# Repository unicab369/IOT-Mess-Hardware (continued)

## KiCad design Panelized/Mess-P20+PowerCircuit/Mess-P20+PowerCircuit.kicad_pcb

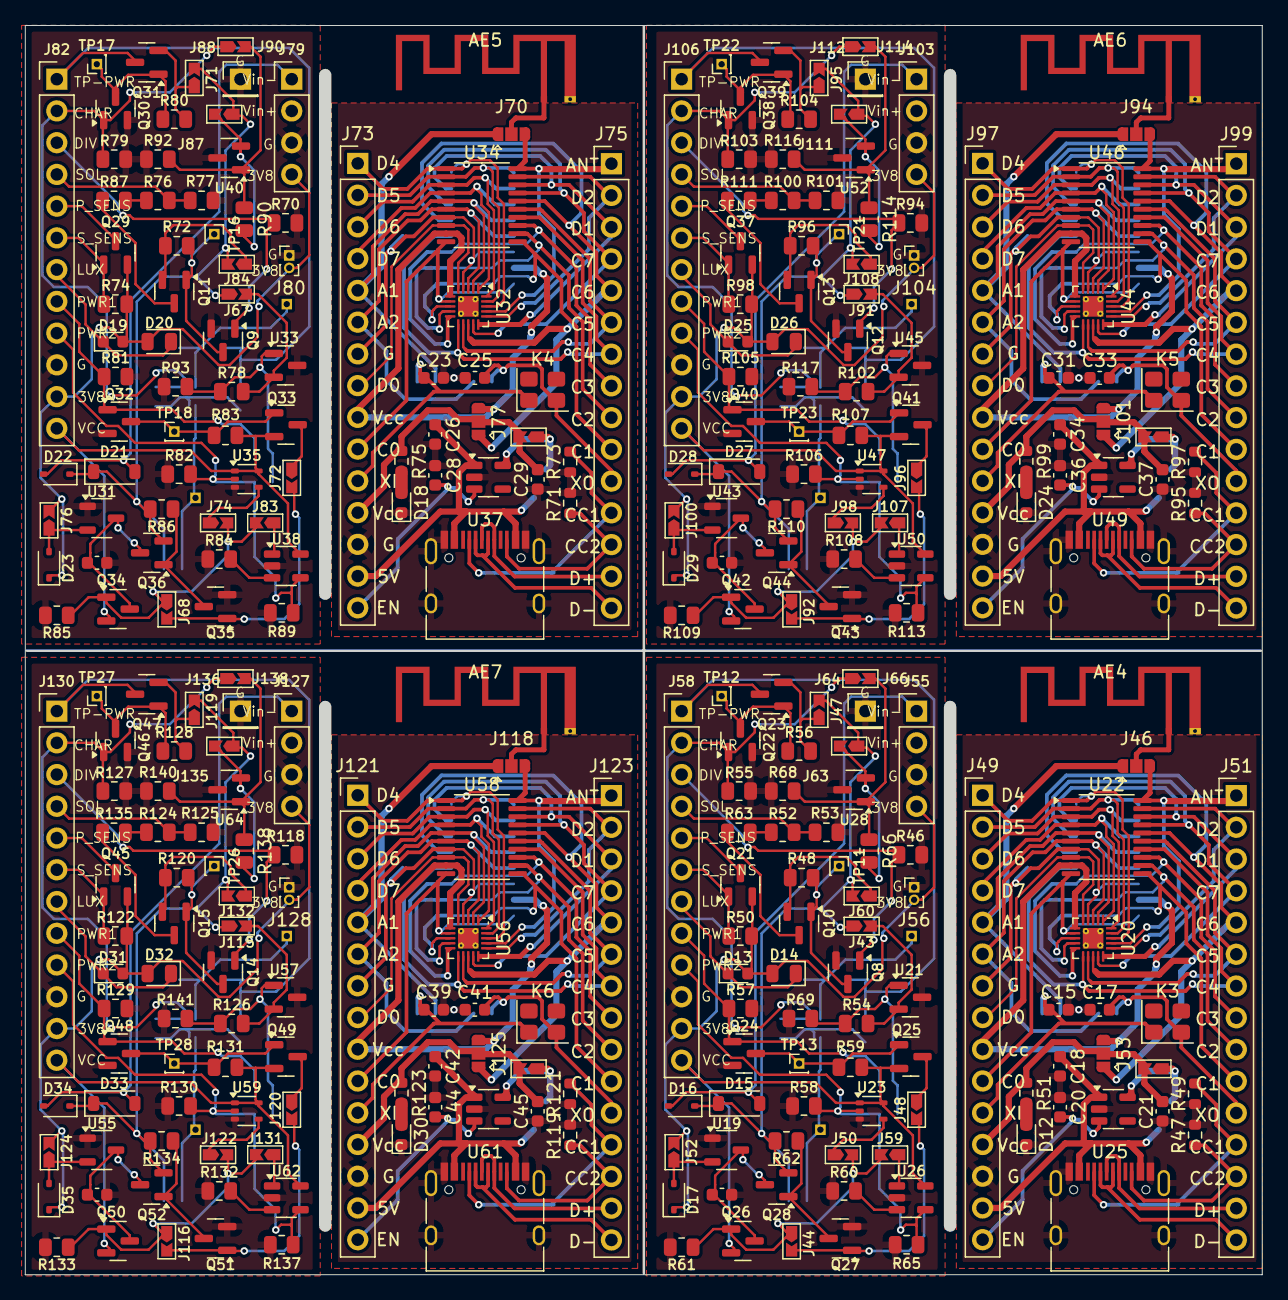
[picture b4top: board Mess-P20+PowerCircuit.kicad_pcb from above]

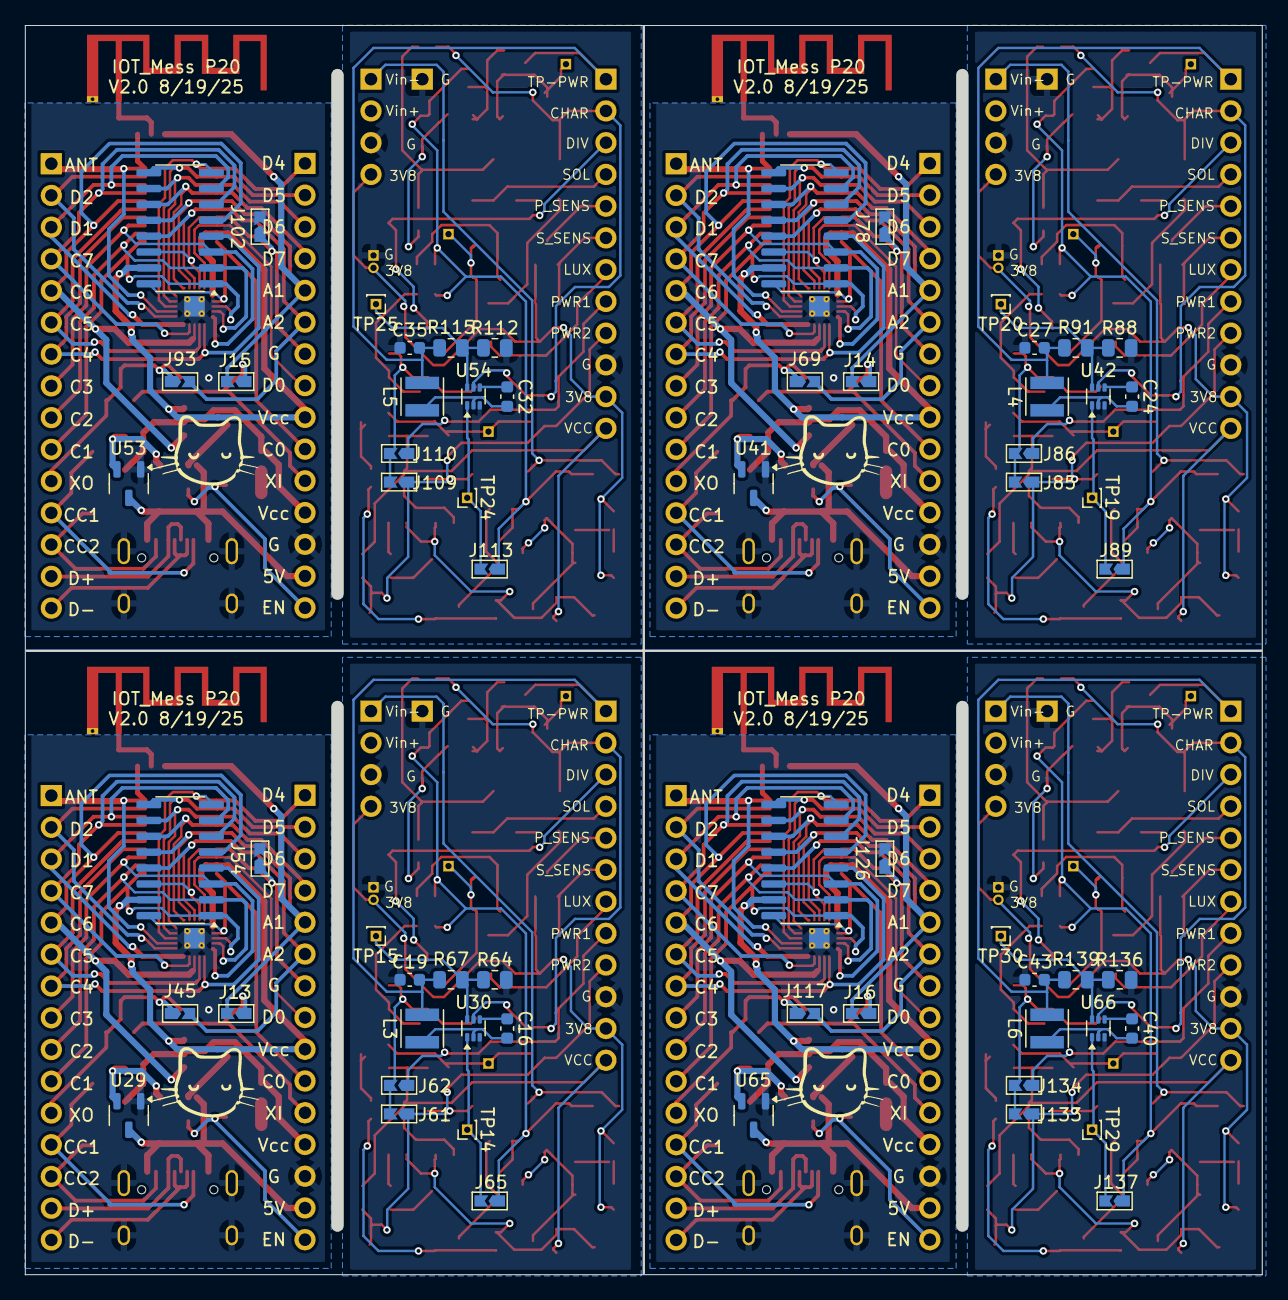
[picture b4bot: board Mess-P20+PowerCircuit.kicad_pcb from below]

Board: 2 copper layers, 99.0 x 100.0 mm, 372 parts (64 on the bottom side), 72 nets.

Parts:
AE4, AE5, AE6, AE7: Antenna_Shield; Texas_SWRA117D_2.4GHz_Left
C14, C16, C19, C22, C24, C27, C30, C32, C35, C38, C40, C43: C; C_0603_1608Metric
C15, C17, C23, C25, C31, C33, C39, C41: 12-25pF; C_0603_1608Metric
C18, C26, C34, C42: 10u; C_0603_1608Metric
C20, C21, C28, C29, C36, C37, C44, C45: 1u; C_0603_1608Metric
D12, D18, D24, D30: LED; LED_0603_1608Metric
D13, D19, D25, D31: D_Photo; LED_0603_1608Metric
D14, D20, D26, D32: D_Photo; LED_0805_2012Metric
D15, D21, D27, D33: MBR0520; D_SOD-123
D16, D17, D22, D23, D28, D29, D34, D35: BAT48JFILM; D_SOD-323
J13, J14, J15, J16, J43, J44, J45, J47, J48, J50, J52, J54, J57, J59, J60, J61, J62, J63, J64, J65, J67, J68, J69, J71, J72, J74, J76, J78, J81, J83, J84, J85, J86, J87, J88, J89, J91, J92, J93, J95, J96, J98, J100, J102, J105, J107, J108, J109, J110, J111, J112, J113, J115, J116, J117, J119, J120, J122, J124, J126, J129, J131, J132, J133, J134, J135, J136, J137: Jumper_2; Jumpper-triangle
J46, J53, J70, J77, J94, J101, J118, J125: Jumper; Jumper-3_P1.3mm_Open_RoundedPad1.0x1.5mm
J49, J51, J73, J75, J97, J99, J121, J123: Conn_01x15_Pin; PinHeader_1x15_P2.54mm_Vertical
J55, J79, J103, J127: Conn_01x04_Pin; PinHeader_1x04_P2.54mm_Vertical
J56, J80, J104, J128: Conn_01x02_Pin; PinHeader_1x02_P1.00mm_Vertical
J58, J82, J106, J130: Conn_01x12_Pin; PinHeader_1x12_P2.54mm_Vertical
J66, J90, J114, J138: Conn_01x01_Pin; PinHeader_1x01_P2.54mm_Vertical
K3, K4, K5, K6: Crystal; Crystal_SMD_3225-4Pin_3.2x2.5mm
L3, L4, L5, L6: L; L_Neosid_SMS-ME3010
Q8, Q9, Q12, Q14, Q22, Q24, Q27, Q30, Q32, Q35, Q38, Q40, Q43, Q46, Q48, Q51: AO3400A; SOT-23
Q10, Q11, Q13, Q15, Q21, Q23, Q25, Q26, Q28, Q29, Q31, Q33, Q34, Q36, Q37, Q39, Q41, Q42, Q44, Q45, Q47, Q49, Q50, Q52: AO3401A (P-Fet); SOT-23
R46, R50, R55, R57, R58, R59, R61, R62, R70, R74, R79, R81, R82, R83, R85, R86, R94, R98, R103, R105, R106, R107, R109, R110, R118, R122, R127, R129, R130, R131, R133, R134: 100K; R_0805_2012Metric
R47, R49, R71, R73, R95, R97, R119, R121: 5.1K; R_0603_1608Metric
R48, R52, R53, R54, R56, R60, R63, R64, R65, R66, R67, R68, R69, R72, R76, R77, R78, R80, R84, R87, R88, R89, R90, R91, R92, R93, R96, R100, R101, R102, R104, R108, R111, R112, R113, R114, R115, R116, R117, R120, R124, R125, R126, R128, R132, R135, R136, R137, R138, R139, R140, R141: 10K; R_0805_2012Metric
R51, R75, R99, R123: R; R_0603_1608Metric
TP11, TP12, TP13, TP14, TP15, TP16, TP17, TP18, TP19, TP20, TP21, TP22, TP23, TP24, TP25, TP26, TP27, TP28, TP29, TP30: TestPoint; PinHeader_1x01_P1.00mm_Vertical
U19, U29, U31, U41, U43, U53, U55, U65: XC6206PxxxMR; SOT-23-3
U20, U32, U44, U56: QFN-20-1EP_3x3mm_P0.4mm_EP1.65x1.65mm_ThermalVias
U21, U28, U33, U40, U45, U52, U57, U64: LT431 (Voltage Ref); SOT-23
U22, U34, U46, U58: TSSOP-20_4.4x6.5mm_P0.65mm
U23, U35, U47, U59: 74LV1T08GW; SOT-353_SC-70-5
U24, U36, U48, U60: SOP-16_3.9x9.9mm_P1.27mm
U25, U37, U49, U61: USB_C_Receptacle_USB2.0_16P; USB_C_Receptacle_HRO_TYPE-C-31-M-12
U26, U38, U50, U62: MT9700; SOT-23-5
U27, U39, U51, U63: ME6211C33M5; SOT-23-5
U30, U42, U54, U66: TPS562202; SOT-563

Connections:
5V: C18.1, C26.1, C34.1, C42.1, J49.14, J73.14, J97.14, J121.14, U25.A4 (VBUS), U25.A9 (VBUS), U25.B4 (VBUS), U25.B9 (VBUS), U27.1 (V_{IN}), U29.3 (VI), U37.A4 (VBUS), U37.A9 (VBUS), U37.B4 (VBUS), U37.B9 (VBUS), U39.1 (V_{IN}), U41.3 (VI), U49.A4 (VBUS), U49.A9 (VBUS), U49.B4 (VBUS), U49.B9 (VBUS), U51.1 (V_{IN}), U53.3 (VI), U61.A4 (VBUS), U61.A9 (VBUS), U61.B4 (VBUS), U61.B9 (VBUS), U63.1 (V_{IN}), U65.3 (VI)
+3.3V: C21.1, C29.1, C37.1, C45.1, J49.12, J53.2 (C), J57.2 (B), J73.12, J77.2 (C), J81.2 (B), J97.12, J101.2 (C), J105.2 (B), J121.12, J125.2 (C), J129.2 (B), R51.1, R75.1, R99.1, R123.1
+3V8: D13.2 (A), D14.2 (A), D17.1 (K), D19.2 (A), D20.2 (A), D23.1 (K), D25.2 (A), D26.2 (A), D29.1 (K), D31.2 (A), D32.2 (A), D35.1 (K), J52.2 (B), J55.4, J56.2, J58.11, J76.2 (B), J79.4, J80.2, J82.11, J100.2 (B), J103.4, J104.2, J106.11, J124.2 (B), J127.4, J128.2, J130.11, Q21.2 (S), Q29.2 (S), Q37.2 (S), Q45.2 (S), R50.2, R74.2, R98.2, R122.2
ADC_LUX: D13.1 (K), D14.1 (K), D19.1 (K), D20.1 (K), D25.1 (K), D26.1 (K), D31.1 (K), D32.1 (K), J58.7, J82.7, J106.7, J130.7
ADC_SOLAR: J58.4, J82.4, J106.4, J130.4, R52.1, R53.2, R76.1, R77.2, R100.1, R101.2, R124.1, R125.2
ANT: AE4.1 (A), AE5.1 (A), AE6.1 (A), AE7.1 (A), J46.2 (C), J70.2 (C), J94.2 (C), J118.2 (C)
CC1: J51.12, J75.12, J99.12, J123.12, R49.1, R73.1, R97.1, R121.1, U25.A5 (CC1), U37.A5 (CC1), U49.A5 (CC1), U61.A5 (CC1)
CC2: J51.13, J75.13, J99.13, J123.13, R47.1, R71.1, R95.1, R119.1, U25.B5 (CC2), U37.B5 (CC2), U49.B5 (CC2), U61.B5 (CC2)
D+: J51.14, J75.14, J99.14, J123.14, U25.A6 (D+), U25.B6 (D+), U37.A6 (D+), U37.B6 (D+), U49.A6 (D+), U49.B6 (D+), U61.A6 (D+), U61.B6 (D+)
D-: J51.15, J75.15, J99.15, J123.15, U25.A7 (D-), U25.B7 (D-), U37.A7 (D-), U37.B7 (D-), U49.A7 (D-), U49.B7 (D-), U61.A7 (D-), U61.B7 (D-)
GND: C14.2, C19.1, C22.2, C27.1, C30.2, C35.1, C38.2, C43.1, J55.3, J56.1, J58.10, J66.1, J79.3, J80.1, J82.10, J90.1, J103.3, J104.1, J106.10, J114.1, J127.3, J128.1, J130.10, J138.1, Q8.2 (S), Q9.2 (S), Q12.2 (S), Q14.2 (S), Q22.2 (S), Q24.2 (S), Q27.2 (S), Q30.2 (S), Q32.2 (S), Q35.2 (S), Q38.2 (S), Q40.2 (S), Q43.2 (S), Q46.2 (S), Q48.2 (S), Q51.2 (S), R46.1, R53.1, R55.1, R57.1, R58.1, R60.1, R61.1, R64.1, R65.1, R68.1, R69.1, R70.1, R77.1, R79.1, R81.1, R82.1, R84.1, R85.1, R88.1, R89.1, R92.1, R93.1, R94.1, R101.1, R103.1, R105.1, R106.1, R108.1, R109.1, R112.1, R113.1, R116.1, R117.1, R118.1, R125.1, R127.1, R129.1, R130.1, R132.1, R133.1, R136.1, R137.1, R140.1, R141.1, U19.1 (GND), U21.3 (GND), U23.3 (GND), U26.2 (GND), U28.3 (GND), U30.3 (GND), U31.1 (GND), U33.3 (GND), U35.3 (GND), U38.2 (GND), U40.3 (GND), U42.3 (GND), U43.1 (GND), U45.3 (GND), U47.3 (GND), U50.2 (GND), U52.3 (GND), U54.3 (GND), U55.1 (GND), U57.3 (GND), U59.3 (GND), U62.2 (GND), U64.3 (GND), U66.3 (GND)
IN-: D15.2 (A), D16.2 (A), D21.2 (A), D22.2 (A), D27.2 (A), D28.2 (A), D33.2 (A), D34.2 (A), J55.1, J79.1, J103.1, J127.1
LDO_EN: C20.1, C28.1, C36.1, C44.1, J49.15, J73.15, J97.15, J121.15, U27.3 (CE), U39.3 (CE), U51.3 (CE), U63.3 (CE)
unnamed: D12.2 (A), D18.2 (A), D24.2 (A), D30.2 (A), R51.2, R75.2, R99.2, R123.2
unnamed: D15.1 (K), D16.1 (K), D21.1 (K), D22.1 (K), D27.1 (K), D28.1 (K), D33.1 (K), D34.1 (K), J43.2 (B), J47.2 (B), J60.1 (A), J63.1 (A), J65.1 (A), J67.2 (B), J71.2 (B), J84.1 (A), J87.1 (A), J89.1 (A), J91.2 (B), J95.2 (B), J108.1 (A), J111.1 (A), J113.1 (A), J115.2 (B), J119.2 (B), J132.1 (A), J135.1 (A), J137.1 (A), Q28.2 (S), Q36.2 (S), Q44.2 (S), Q52.2 (S), R62.2, R86.2, R110.2, R134.2
unnamed: D17.2 (A), D23.2 (A), D29.2 (A), D35.2 (A), J52.1 (A), J76.1 (A), J100.1 (A), J124.1 (A), U19.2 (VO), U31.2 (VO), U43.2 (VO), U55.2 (VO)
unnamed: J43.1 (A), J67.1 (A), J91.1 (A), J115.1 (A), Q10.2 (S), Q11.2 (S), Q13.2 (S), Q15.2 (S), R48.2, R72.2, R96.2, R120.2
unnamed: J44.2 (B), J48.2 (B), J68.2 (B), J72.2 (B), J92.2 (B), J96.2 (B), J116.2 (B), J120.2 (B), Q27.1 (G), Q35.1 (G), Q43.1 (G), Q51.1 (G)
unnamed: J47.1 (A), J71.1 (A), J95.1 (A), J119.1 (A), Q23.2 (S), Q31.2 (S), Q39.2 (S), Q47.2 (S), R56.2, R80.2, R104.2, R128.2
unnamed: J48.1 (A), J72.1 (A), J96.1 (A), J120.1 (A), Q25.3 (D), Q33.3 (D), Q41.3 (D), Q49.3 (D)
unnamed: J50.1 (A), J74.1 (A), J98.1 (A), J122.1 (A), U23.4 (Y), U35.4 (Y), U47.4 (Y), U59.4 (Y)
unnamed: J57.1 (A), J81.1 (A), J105.1 (A), J129.1 (A), U27.5 (V_{OUT}), U29.2 (VO), U39.5 (V_{OUT}), U41.2 (VO), U51.5 (V_{OUT}), U53.2 (VO), U63.5 (V_{OUT}), U65.2 (VO)
unnamed: J59.1 (A), J83.1 (A), J107.1 (A), J131.1 (A), U26.1 (OUT), U38.1 (OUT), U50.1 (OUT), U62.1 (OUT)
unnamed: J44.1 (A), J50.2 (B), J59.2 (B), J68.1 (A), J74.2 (B), J83.2 (B), J92.1 (A), J98.2 (B), J107.2 (B), J116.1 (A), J122.2 (B), J131.2 (B), Q26.1 (G), Q34.1 (G), Q42.1 (G), Q50.1 (G), R61.2, R85.2, R109.2, R133.2
unnamed: J60.2 (B), J84.2 (B), J108.2 (B), J132.2 (B), R54.2, R78.2, R102.2, R126.2, U21.2 (VDD), U33.2 (VDD), U45.2 (VDD), U57.2 (VDD)
unnamed: J61.2 (B), J62.2 (B), J85.2 (B), J86.2 (B), J109.2 (B), J110.2 (B), J133.2 (B), J134.2 (B), R54.1, R69.2, R78.1, R93.2, R102.1, R117.2, R126.1, R141.2, U21.1 (VOUT), U33.1 (VOUT), U45.1 (VOUT), U57.1 (VOUT)
unnamed: J63.2 (B), J87.2 (B), J111.2 (B), J135.2 (B), R66.2, R90.2, R114.2, R138.2, U28.2 (VDD), U40.2 (VDD), U52.2 (VDD), U64.2 (VDD)
unnamed: J64.2 (B), J88.2 (B), J112.2 (B), J136.2 (B), R66.1, R68.2, R90.1, R92.2, R114.1, R116.2, R138.1, R140.2, U28.1 (VOUT), U40.1 (VOUT), U52.1 (VOUT), U64.1 (VOUT)
unnamed: J65.2 (B), J89.2 (B), J113.2 (B), J137.2 (B), TP14.1, TP19.1, TP24.1, TP29.1, U30.1 (VIN), U42.1 (VIN), U54.1 (VIN), U66.1 (VIN)
unnamed: Q8.3 (D), Q9.3 (D), Q10.1 (G), Q11.1 (G), Q12.3 (D), Q13.1 (G), Q14.3 (D), Q15.1 (G), R48.1, R72.1, R96.1, R120.1, TP11.1, TP16.1, TP21.1, TP26.1
unnamed: Q10.3 (D), Q11.3 (D), Q13.3 (D), Q15.3 (D), R63.2, R87.2, R111.2, R135.2
unnamed: Q22.3 (D), Q23.1 (G), Q30.3 (D), Q31.1 (G), Q38.3 (D), Q39.1 (G), Q46.3 (D), Q47.1 (G), R56.1, R80.1, R104.1, R128.1, TP12.1, TP17.1, TP22.1, TP27.1
unnamed: Q24.3 (D), Q25.1 (G), Q32.3 (D), Q33.1 (G), Q40.3 (D), Q41.1 (G), Q48.3 (D), Q49.1 (G), R59.1, R83.1, R107.1, R131.1, TP13.1, TP18.1, TP23.1, TP28.1
unnamed: C14.1, C22.1, C30.1, C38.1, Q26.3 (D), Q28.3 (D), Q34.3 (D), Q36.3 (D), Q42.3 (D), Q44.3 (D), Q50.3 (D), Q52.3 (D), U19.3 (VI), U31.3 (VI), U43.3 (VI), U55.3 (VI)
unnamed: Q27.3 (D), Q28.1 (G), Q35.3 (D), Q36.1 (G), Q43.3 (D), Q44.1 (G), Q51.3 (D), Q52.1 (G), R62.1, R86.1, R110.1, R134.1
unnamed: R52.2, R63.1, R76.2, R87.1, R100.2, R111.1, R124.2, R135.1
unnamed: R60.2, R84.2, R108.2, R132.2, U26.3 (SET), U38.3 (SET), U50.3 (SET), U62.3 (SET)
unnamed: C16.2, C24.2, C32.2, C40.2, L3.1, L4.1, L5.1, L6.1, U30.2 (SW), U42.2 (SW), U54.2 (SW), U66.2 (SW)
unnamed: C16.1, C24.1, C32.1, C40.1, U30.4 (VBST), U42.4 (VBST), U54.4 (VBST), U66.4 (VBST)
unnamed: R64.2, R67.2, R88.2, R91.2, R112.2, R115.2, R136.2, R139.2, TP15.1, TP20.1, TP25.1, TP30.1, U30.6 (VFB), U42.6 (VFB), U54.6 (VFB), U66.6 (VFB)
OSCI: C15.1, C23.1, C31.1, C39.1, J13.1 (A), J14.1 (A), J15.1 (A), J16.1 (A), J49.11, J73.11, J97.11, J121.11, K3.1, K4.1, K5.1, K6.1
OSCO: C17.1, C25.1, C33.1, C41.1, J45.1 (A), J51.11, J69.1 (A), J75.11, J93.1 (A), J99.11, J117.1 (A), J123.11, K3.2, K4.2, K5.2, K6.2
PWR_SENSORS: J58.5, J82.5, J106.5, J130.5, Q21.3 (D), Q29.3 (D), Q37.3 (D), Q45.3 (D)
P_0: C15.2, C17.2, C18.2, C20.2, C21.2, C23.2, C25.2, C26.2, C28.2, C29.2, C31.2, C33.2, C34.2, C36.2, C37.2, C39.2, C41.2, C42.2, C44.2, C45.2, D12.1 (K), D18.1 (K), D24.1 (K), D30.1 (K), J49.13, J54.2 (B), J73.13, J78.2 (B), J97.13, J102.2 (B), J121.13, J126.2 (B), R47.2, R49.2, R71.2, R73.2, R95.2, R97.2, R119.2, R121.2, U20.21 (GND), U25.A1 (GND), U25.A12 (GND), U25.B1 (GND), U25.B12 (GND), U25.S1 (SHIELD), U27.2 (V_{SS}), U29.1 (GND), U32.21 (GND), U37.A1 (GND), U37.A12 (GND), U37.B1 (GND), U37.B12 (GND), U37.S1 (SHIELD), U39.2 (V_{SS}), U41.1 (GND), U44.21 (GND), U49.A1 (GND), U49.A12 (GND), U49.B1 (GND), U49.B12 (GND), U49.S1 (SHIELD), U51.2 (V_{SS}), U53.1 (GND), U56.21 (GND), U61.A1 (GND), U61.A12 (GND), U61.B1 (GND), U61.B12 (GND), U61.S1 (SHIELD), U63.2 (V_{SS}), U65.1 (GND)
P_1: J49.1, J73.1, J97.1, J121.1, U20.18 (PD4/A7), U22.1 (PD4/A7), U24.8 (PD4/A7), U32.18 (PD4/A7), U34.1 (PD4/A7), U36.8 (PD4/A7), U44.18 (PD4/A7), U46.1 (PD4/A7), U48.8 (PD4/A7), U56.18 (PD4/A7), U58.1 (PD4/A7), U60.8 (PD4/A7)
P_2: J49.2, J73.2, J97.2, J121.2, U20.19 (PD5/A5/UTX/VDD*), U22.2 (PD5/A5/OSCI*), U24.9 (PD5/A5/UTX), U32.19 (PD5/A5/UTX/VDD*), U34.2 (PD5/A5/OSCI*), U36.9 (PD5/A5/UTX), U44.19 (PD5/A5/UTX/VDD*), U46.2 (PD5/A5/OSCI*), U48.9 (PD5/A5/UTX), U56.19 (PD5/A5/UTX/VDD*), U58.2 (PD5/A5/OSCI*), U60.9 (PD5/A5/UTX)
P_3: J49.3, J73.3, J97.3, J121.3, U20.20 (PD6/A6/URX/ANT*), U22.3 (PD6/A6/OSCO*), U24.10 (PD6/A6/URX), U32.20 (PD6/A6/URX/ANT*), U34.3 (PD6/A6/OSCO*), U36.10 (PD6/A6/URX), U44.20 (PD6/A6/URX/ANT*), U46.3 (PD6/A6/OSCO*), U48.10 (PD6/A6/URX), U56.20 (PD6/A6/URX/ANT*), U58.3 (PD6/A6/OSCO*), U60.10 (PD6/A6/URX)
P_4: J49.4, J73.4, J97.4, J121.4, U20.1 (PD7/NRST), U22.4 (PD7/RST), U24.11 (PD7/NRST), U32.1 (PD7/NRST), U34.4 (PD7/RST), U36.11 (PD7/NRST), U44.1 (PD7/NRST), U46.4 (PD7/RST), U48.11 (PD7/NRST), U56.1 (PD7/NRST), U58.4 (PD7/RST), U60.11 (PD7/NRST)
P_5: J13.2 (B), J14.2 (B), J15.2 (B), J16.2 (B), J46.1 (A), J49.5, J70.1 (A), J73.5, J94.1 (A), J97.5, J118.1 (A), J121.5, U20.2 (PA1/OSCI), U22.5 (PA1/OSCI), U24.12 (PA1/A1/OSC_IN), U32.2 (PA1/OSCI), U34.5 (PA1/OSCI), U36.12 (PA1/A1/OSC_IN), U44.2 (PA1/OSCI), U46.5 (PA1/OSCI), U48.12 (PA1/A1/OSC_IN), U56.2 (PA1/OSCI), U58.5 (PA1/OSCI), U60.12 (PA1/A1/OSC_IN)
P_6: J45.2 (B), J49.6, J69.2 (B), J73.6, J93.2 (B), J97.6, J117.2 (B), J121.6, U20.3 (PA2/OSCO), U22.6 (PA2/OSCO), U24.13 (PA2/A0/OSC_OUT), U32.3 (PA2/OSCO), U34.6 (PA2/OSCO), U36.13 (PA2/A0/OSC_OUT), U44.3 (PA2/OSCO), U46.6 (PA2/OSCO), U48.13 (PA2/A0/OSC_OUT), U56.3 (PA2/OSCO), U58.6 (PA2/OSCO), U60.13 (PA2/A0/OSC_OUT)
P_7: J49.7, J54.1 (A), J73.7, J78.1 (A), J97.7, J102.1 (A), J121.7, J126.1 (A), U20.4 (VSS), U22.7 (VSS), U24.14 (GND), U32.4 (VSS), U34.7 (VSS), U36.14 (GND), U44.4 (VSS), U46.7 (VSS), U48.14 (GND), U56.4 (VSS), U58.7 (VSS), U60.14 (GND)
P_8: J49.8, J73.8, J97.8, J121.8, U20.5 (PD0/ANT*(57x)), U22.8 (PD0), U32.5 (PD0/ANT*(57x)), U34.8 (PD0), U44.5 (PD0/ANT*(57x)), U46.8 (PD0), U56.5 (PD0/ANT*(57x)), U58.8 (PD0)
P_9: J49.9, J53.3 (B), J73.9, J77.3 (B), J97.9, J101.3 (B), J121.9, J125.3 (B), U20.6 (VDD), U22.9 (VDD), U24.15 (VDD), U32.6 (VDD), U34.9 (VDD), U36.15 (VDD), U44.6 (VDD), U46.9 (VDD), U48.15 (VDD), U56.6 (VDD), U58.9 (VDD), U60.15 (VDD)
P_10: J49.10, J73.10, J97.10, J121.10, U20.7 (PC0), U22.10 (PC0), U24.16 (PC0), U32.7 (PC0), U34.10 (PC0), U36.16 (PC0), U44.7 (PC0), U46.10 (PC0), U48.16 (PC0), U56.7 (PC0), U58.10 (PC0), U60.16 (PC0)
P_11: J51.10, J75.10, J99.10, J123.10, U20.8 (PC1/SDA), U22.11 (PC1/SDA), U24.1 (PC1/SDA), U32.8 (PC1/SDA), U34.11 (PC1/SDA), U36.1 (PC1/SDA), U44.8 (PC1/SDA), U46.11 (PC1/SDA), U48.1 (PC1/SDA), U56.8 (PC1/SDA), U58.11 (PC1/SDA), U60.1 (PC1/SDA)
P_12: J51.9, J75.9, J99.9, J123.9, U20.9 (PC2/SCL), U22.12 (PC2/SCL), U24.2 (PC2/SCL), U32.9 (PC2/SCL), U34.12 (PC2/SCL), U36.2 (PC2/SCL), U44.9 (PC2/SCL), U46.12 (PC2/SCL), U48.2 (PC2/SCL), U56.9 (PC2/SCL), U58.12 (PC2/SCL), U60.2 (PC2/SCL)
P_13: J51.8, J75.8, J99.8, J123.8, U20.10 (PC3/RST*), U22.13 (PC3), U24.3 (PC3), U32.10 (PC3/RST*), U34.13 (PC3), U36.3 (PC3), U44.10 (PC3/RST*), U46.13 (PC3), U48.3 (PC3), U56.10 (PC3/RST*), U58.13 (PC3), U60.3 (PC3)
P_14: J51.7, J75.7, J99.7, J123.7, U20.11 (PC4/A2), U22.14 (PC4/A2), U24.4 (PC4/A2), U32.11 (PC4/A2), U34.14 (PC4/A2), U36.4 (PC4/A2), U44.11 (PC4/A2), U46.14 (PC4/A2), U48.4 (PC4/A2), U56.11 (PC4/A2), U58.14 (PC4/A2), U60.4 (PC4/A2)
P_15: J51.6, J75.6, J99.6, J123.6, U20.12 (PC5/X32MO*), U22.15 (PC5/VSS*), U32.12 (PC5/X32MO*), U34.15 (PC5/VSS*), U44.12 (PC5/X32MO*), U46.15 (PC5/VSS*), U56.12 (PC5/X32MO*), U58.15 (PC5/VSS*)
P_16: J51.5, J53.1 (A), J75.5, J77.1 (A), J99.5, J101.1 (A), J123.5, J125.1 (A), U20.13 (PC6/MOSI/X32MI*), U22.16 (PC6/MOSI/VDD*), U24.5 (PC6/MOSI), U32.13 (PC6/MOSI/X32MI*), U34.16 (PC6/MOSI/VDD*), U36.5 (PC6/MOSI), U44.13 (PC6/MOSI/X32MI*), U46.16 (PC6/MOSI/VDD*), U48.5 (PC6/MOSI), U56.13 (PC6/MOSI/X32MI*), U58.16 (PC6/MOSI/VDD*), U60.5 (PC6/MOSI)
P_17: J51.4, J75.4, J99.4, J123.4, U20.14 (PC7/MISO), U22.17 (PC7/MISO/UDM*), U24.6 (PC7/MISO), U32.14 (PC7/MISO), U34.17 (PC7/MISO/UDM*), U36.6 (PC7/MISO), U44.14 (PC7/MISO), U46.17 (PC7/MISO/UDM*), U48.6 (PC7/MISO), U56.14 (PC7/MISO), U58.17 (PC7/MISO/UDM*), U60.6 (PC7/MISO)
P_18: J51.3, J75.3, J99.3, J123.3, U20.15 (PD1/SWIO/ANT*), U22.18 (PD1/SWIO/UDP*), U24.7 (PD1/SWIO), U32.15 (PD1/SWIO/ANT*), U34.18 (PD1/SWIO/UDP*), U36.7 (PD1/SWIO), U44.15 (PD1/SWIO/ANT*), U46.18 (PD1/SWIO/UDP*), U48.7 (PD1/SWIO), U56.15 (PD1/SWIO/ANT*), U58.18 (PD1/SWIO/UDP*), U60.7 (PD1/SWIO)
P_19: J51.2, J75.2, J99.2, J123.2, U20.16 (PD2/A3/UDP*), U22.19 (PD2/A3/SWIO*), U32.16 (PD2/A3/UDP*), U34.19 (PD2/A3/SWIO*), U44.16 (PD2/A3/UDP*), U46.19 (PD2/A3/SWIO*), U56.16 (PD2/A3/UDP*), U58.19 (PD2/A3/SWIO*)
P_20: J46.3 (B), J51.1, J70.3 (B), J75.1, J94.3 (B), J99.1, J118.3 (B), J123.1, U20.17 (PD3/A4/UDM*), U22.20 (PD3/A4/ANT*), U32.17 (PD3/A4/UDM*), U34.20 (PD3/A4/ANT*), U44.17 (PD3/A4/UDM*), U46.20 (PD3/A4/ANT*), U56.17 (PD3/A4/UDM*), U58.20 (PD3/A4/ANT*)
SOLAR/IN+: J55.2, J79.2, J103.2, J127.2
SW_CHARGER: J58.2, J64.1 (A), J82.2, J88.1 (A), J106.2, J112.1 (A), J130.2, J136.1 (A), Q22.1 (G), Q30.1 (G), Q38.1 (G), Q46.1 (G), R55.2, R79.2, R103.2, R127.2, U30.5 (EN), U42.5 (EN), U54.5 (EN), U66.5 (EN)
SW_DIVIDER: J58.3, J82.3, J106.3, J130.3, Q8.1 (G), Q9.1 (G), Q12.1 (G), Q14.1 (G), R46.2, R70.2, R94.2, R118.2
SW_PWR1: J58.8, J62.1 (A), J82.8, J86.1 (A), J106.8, J110.1 (A), J130.8, J134.1 (A), Q24.1 (G), Q32.1 (G), Q40.1 (G), Q48.1 (G), R57.2, R81.2, R105.2, R129.2
SW_PWR2: J58.9, J61.1 (A), J82.9, J85.1 (A), J106.9, J109.1 (A), J130.9, J133.1 (A), R58.2, R65.2, R82.2, R89.2, R106.2, R113.2, R130.2, R137.2, U23.2 (A), U26.4 (ON), U35.2 (A), U38.4 (ON), U47.2 (A), U50.4 (ON), U59.2 (A), U62.4 (ON)
SW_SENSORS: J58.6, J82.6, J106.6, J130.6, Q21.1 (G), Q29.1 (G), Q37.1 (G), Q45.1 (G), R50.1, R74.1, R98.1, R122.1
TP4056_PWR: C19.2, C27.2, C35.2, C43.2, J58.1, J82.1, J106.1, J130.1, L3.2, L4.2, L5.2, L6.2, Q23.3 (D), Q31.3 (D), Q39.3 (D), Q47.3 (D), R67.1, R91.1, R115.1, R139.1
VCC/BATT: J58.12, J82.12, J106.12, J130.12, Q25.2 (S), Q26.2 (S), Q33.2 (S), Q34.2 (S), Q41.2 (S), Q42.2 (S), Q49.2 (S), Q50.2 (S), R59.2, R83.2, R107.2, R131.2, U23.1 (B), U23.5 (VCC), U26.5 (IN), U35.1 (B), U35.5 (VCC), U38.5 (IN), U47.1 (B), U47.5 (VCC), U50.5 (IN), U59.1 (B), U59.5 (VCC), U62.5 (IN)
